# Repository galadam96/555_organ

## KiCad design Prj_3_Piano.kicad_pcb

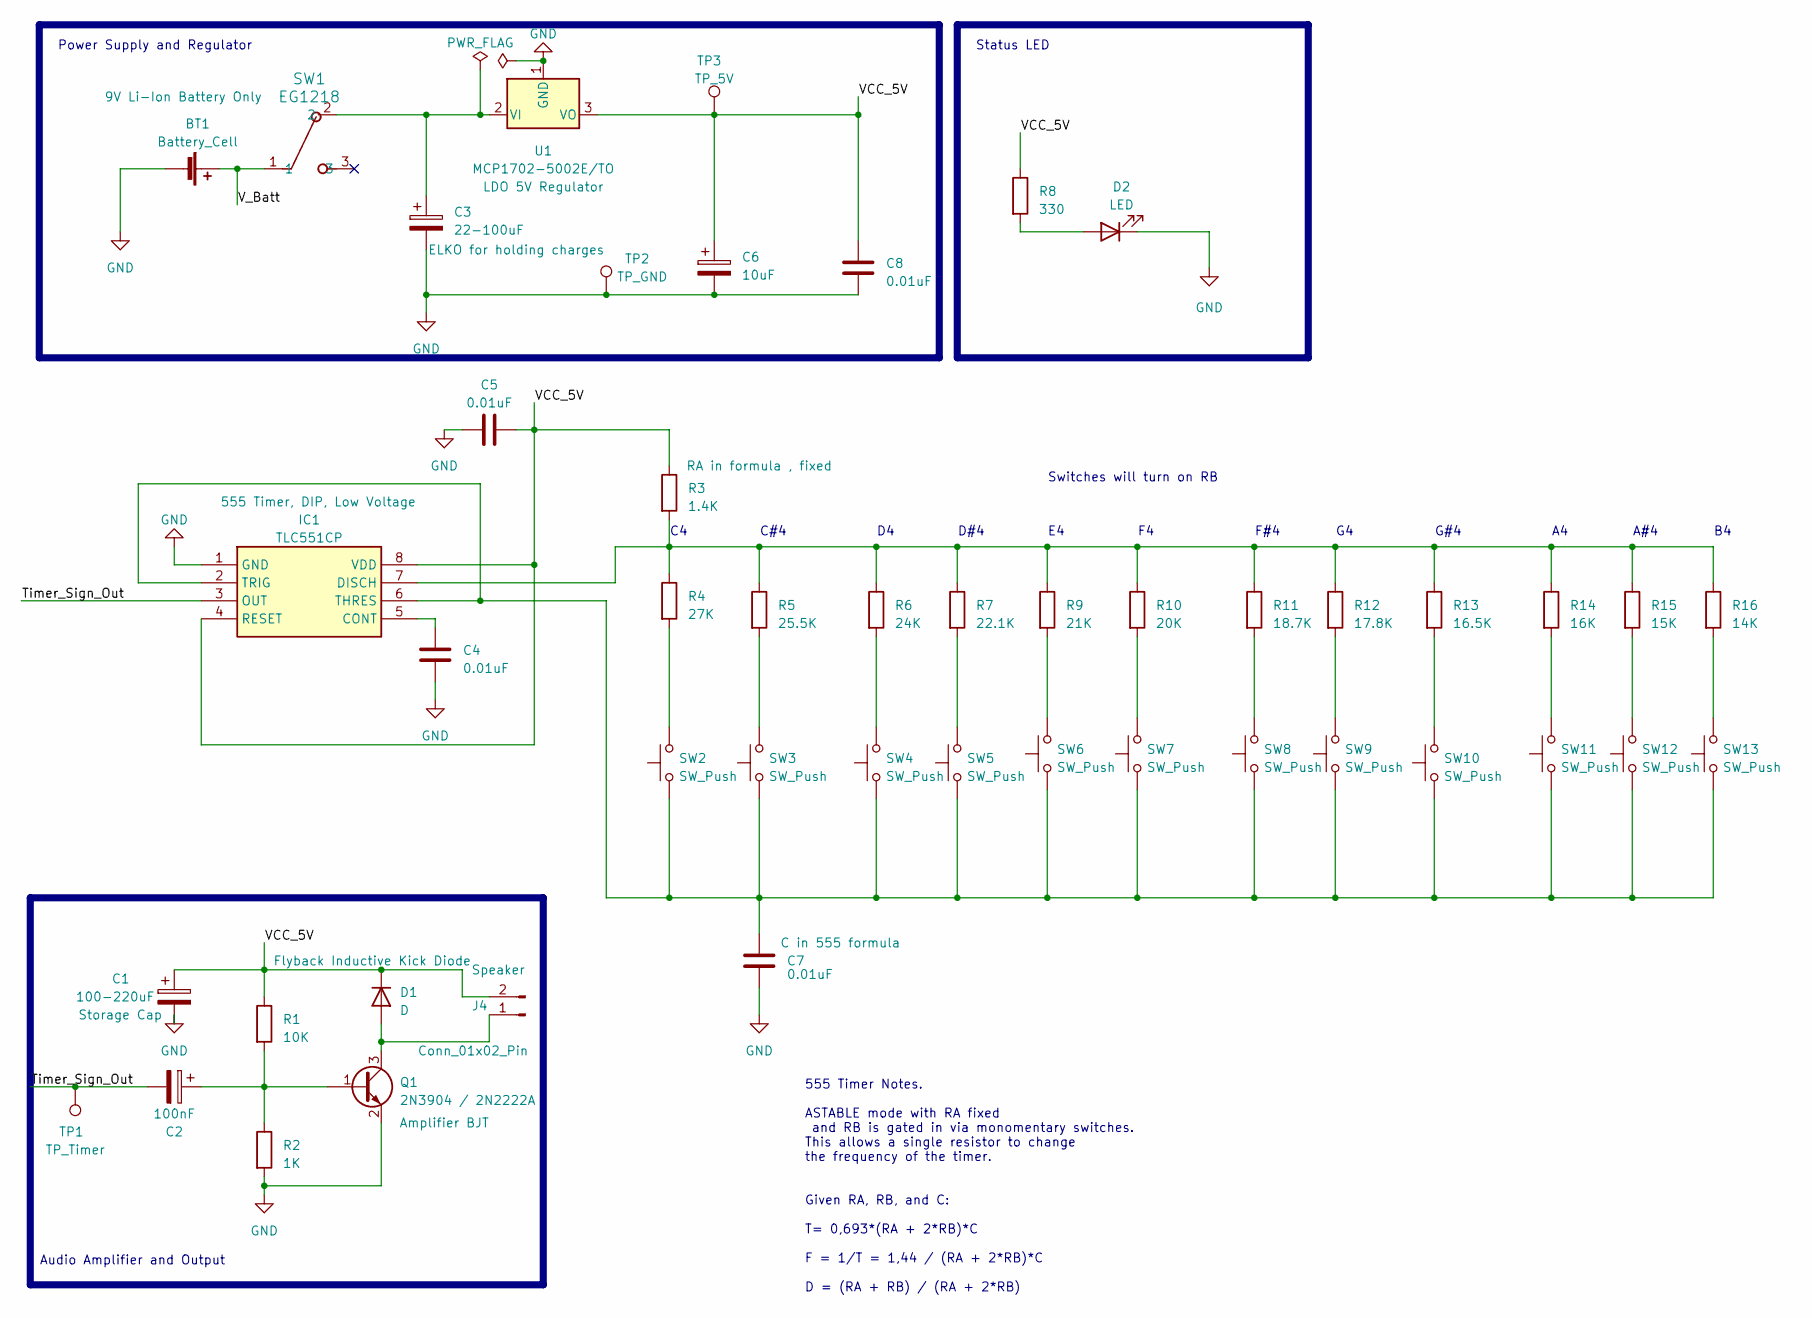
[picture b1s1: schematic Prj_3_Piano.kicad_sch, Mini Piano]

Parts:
BT1: Battery_Cell; KeyStone_1294_Battery_Holder
C1: 100-220uF; CP_Radial_D5.0mm_P2.00mm
C2: 100nF; CP_Radial_D5.0mm_P2.00mm
C3: 22-100uF; CP_Radial_D5.0mm_P2.00mm
C4, C5, C7, C8: 0.01uF; CP_Radial_D8.0mm_P5.00mm
C6: 10uF; CP_Radial_D5.0mm_P2.00mm
D1: D; D_DO-41_SOD81_P10.16mm_Horizontal
D2: LED; LED_D5.0mm
IC1: TLC551CP; Mouser Part Number 595-TLC551CP
J4: Conn_01x02_Pin; PinHeader_1x02_P2.54mm_Vertical
Q1: 2N3904 / 2N2222A; TO-92_Inline
R1: 10K; R_Axial_DIN0207_L6.3mm_D2.5mm_P10.16mm_Horizontal
R2: 1K; R_Axial_DIN0207_L6.3mm_D2.5mm_P10.16mm_Horizontal
R3: 1.4K; R_Axial_DIN0207_L6.3mm_D2.5mm_P10.16mm_Horizontal
R4: 27K; R_Axial_DIN0207_L6.3mm_D2.5mm_P10.16mm_Horizontal
R5: 25.5K; R_Axial_DIN0207_L6.3mm_D2.5mm_P10.16mm_Horizontal
R6: 24K; R_Axial_DIN0207_L6.3mm_D2.5mm_P10.16mm_Horizontal
R7: 22.1K; R_Axial_DIN0207_L6.3mm_D2.5mm_P10.16mm_Horizontal
R8: 330; R_Axial_DIN0207_L6.3mm_D2.5mm_P10.16mm_Horizontal
R9: 21K; R_Axial_DIN0207_L6.3mm_D2.5mm_P10.16mm_Horizontal
R10: 20K; R_Axial_DIN0207_L6.3mm_D2.5mm_P10.16mm_Horizontal
R11: 18.7K; R_Axial_DIN0207_L6.3mm_D2.5mm_P10.16mm_Horizontal
R12: 17.8K; R_Axial_DIN0207_L6.3mm_D2.5mm_P10.16mm_Horizontal
R13: 16.5K; R_Axial_DIN0207_L6.3mm_D2.5mm_P10.16mm_Horizontal
R14: 16K; R_Axial_DIN0207_L6.3mm_D2.5mm_P10.16mm_Horizontal
R15: 15K; R_Axial_DIN0207_L6.3mm_D2.5mm_P10.16mm_Horizontal
R16: 14K; R_Axial_DIN0207_L6.3mm_D2.5mm_P10.16mm_Horizontal
SW1: EG1218
SW2, SW3, SW4, SW5, SW6, SW7, SW8, SW9, SW10, SW11, SW12, SW13: SW_Push; SW_PUSH_6mm
TP1, TP2, TP3: TestPoint_Pad_2.0x2.0mm
U1: MCP1702-5002E/TO; TO-92_Inline

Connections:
/Timer_Sign_Out: C2.2, IC1.3 (OUT), TP1.1
/VCC_5V: C1.1, C5.2, C6.1, C8.1, D1.1 (K), IC1.4 (RESET), IC1.8 (VDD), R1.1, R3.1, R8.1, TP3.1, U1.3 (VO); also elsewhere on the board
/V_Batt: BT1.1 (+), SW1.1
GND: BT1.2 (-), C1.2, C3.2, C4.2, C5.1, C6.2, C7.2, C8.2, D2.1 (K), IC1.1 (GND), Q1.2 (E), R2.2, TP2.1, U1.1 (GND)
unnamed 4: D1.2 (A), Q1.3 (C); also elsewhere on the board
unnamed: D2.2 (A), R8.2
unnamed: C4.1, IC1.5 (CONT)
unnamed: IC1.7 (DISCH), R3.2, R4.1, R5.1, R6.1, R7.1, R9.1, R10.1, R11.1, R12.1, R13.1, R14.1, R15.1, R16.1
unnamed: C7.1, IC1.2 (TRIG), IC1.6 (THRES), SW2.1, SW3.1, SW4.1, SW5.1, SW6.1, SW7.1, SW8.1, SW9.1, SW10.1, SW11.1, SW12.1, SW13.1
unnamed: C2.1, Q1.1 (B), R1.2, R2.1
unnamed: R4.2, SW2.2
unnamed: R5.2, SW3.2
unnamed: R6.2, SW4.2
unnamed: R7.2, SW5.2
unnamed: R9.2, SW6.2
unnamed: R10.2, SW7.2
unnamed: R11.2, SW8.2
unnamed: R12.2, SW9.2
unnamed: R13.2, SW10.2
unnamed: R14.2, SW11.2
unnamed: R15.2, SW12.2
unnamed: R16.2, SW13.2
unnamed: C3.1, SW1.2, U1.2 (VI)

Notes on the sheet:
Audio Amplifier and Output
D#4
F#4
A#4
C#4
Switches will turn on RB
Power Supply and Regulator
G#4
555 Timer Notes. ASTABLE mode with RA fixed and RB is gated in via monomentary switches. This allows a single resistor to change the frequency of the timer. Given RA, RB, and C: T= 0,693*(RA + 2*RB)*C F = 1/T = 1,44 / (RA + 2*RB)*C D = (RA + RB) / (RA + 2*RB)
Status LED

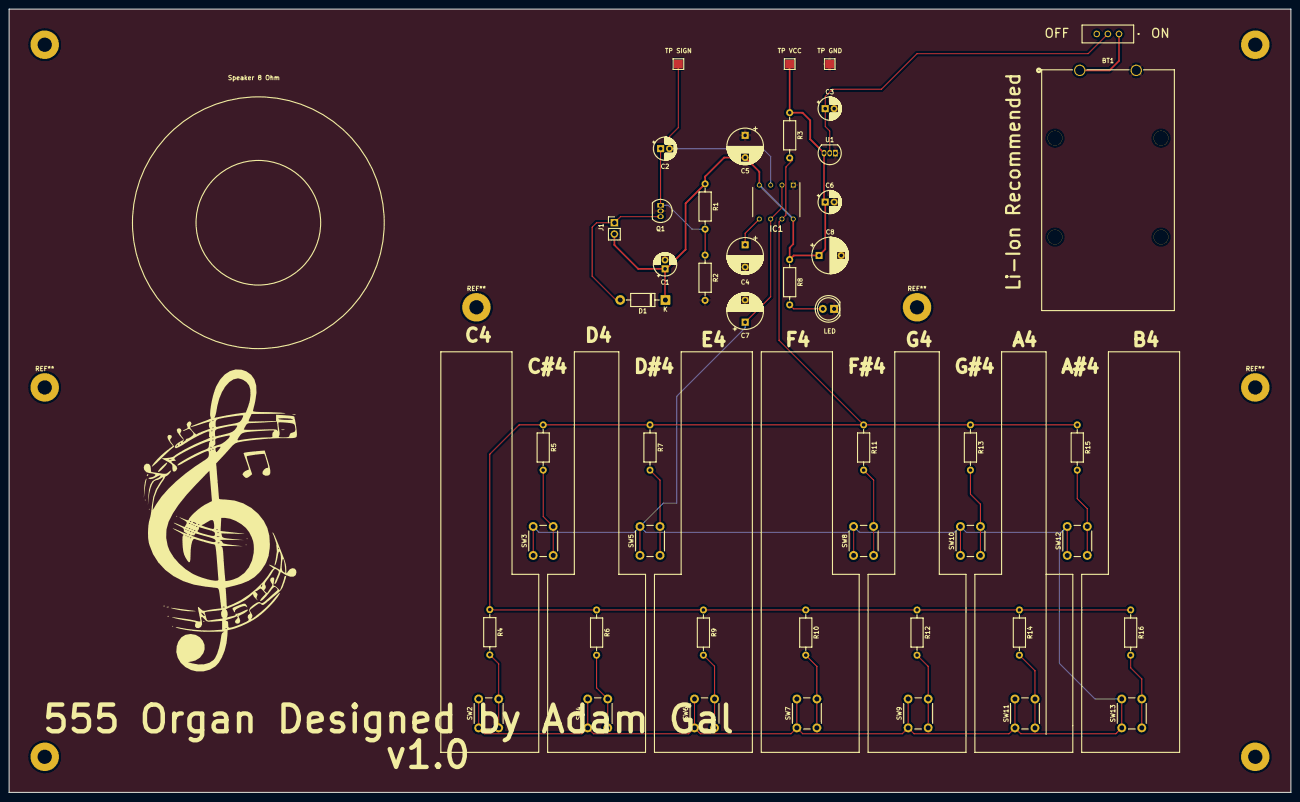
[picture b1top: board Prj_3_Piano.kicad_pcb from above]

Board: 2 copper layers, 288.0 x 176.0 mm, 47 parts (0 on the bottom side), 23 nets.

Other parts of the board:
J1: Conn_01x02_Pin; PinHeader_1x02_P2.54mm_Vertical

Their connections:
/VCC_5V: J1.2; also elsewhere on the board
unnamed 4: J1.1; also elsewhere on the board

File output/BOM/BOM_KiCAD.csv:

"Id";"Designator";"Footprint";"Quantity";"Designation";"Supplier and ref";
1;"R13";"R_Axial_DIN0207_L6.3mm_D2.5mm_P10.16mm_Horizontal";1;"16.5K";;;
2;"R1";"R_Axial_DIN0207_L6.3mm_D2.5mm_P10.16mm_Horizontal";1;"10K";;;
3;"R8";"R_Axial_DIN0207_L6.3mm_D2.5mm_P10.16mm_Horizontal";1;"330";;;
4;"SW5,SW2,SW6,SW8,SW3,SW4,SW10,SW11,SW7,SW13,SW12,SW9";"SW_PUSH_6mm";12;"SW_Push";;;
5;"R10";"R_Axial_DIN0207_L6.3mm_D2.5mm_P10.16mm_Horizontal";1;"20K";;;
6;"C7,C5,C8,C4";"CP_Radial_D8.0mm_P5.00mm";4;"0.01uF";;;
7;"Q1";"TO-92_Inline";1;"2N3904 / 2N2222A";;;
8;"R2";"R_Axial_DIN0207_L6.3mm_D2.5mm_P10.16mm_Horizontal";1;"1K";;;
9;"D1";"D_DO-41_SOD81_P10.16mm_Horizontal";1;"D";;;
10;"TP2,TP3,TP1";"TestPoint_Pad_2.0x2.0mm";3;"~";;;
11;"IC1";"TLC551CP";1;"TLC551CP";;;
12;"R9";"R_Axial_DIN0207_L6.3mm_D2.5mm_P10.16mm_Horizontal";1;"21K";;;
13;"C6";"CP_Radial_D5.0mm_P2.00mm";1;"10uF";;;
14;"U1";"TO-92_Inline";1;"MCP1702-5002E/TO";;;
15;"R5";"R_Axial_DIN0207_L6.3mm_D2.5mm_P10.16mm_Horizontal";1;"25.5K";;;
16;"R6";"R_Axial_DIN0207_L6.3mm_D2.5mm_P10.16mm_Horizontal";1;"24K";;;
17;"R12";"R_Axial_DIN0207_L6.3mm_D2.5mm_P10.16mm_Horizontal";1;"17.8K";;;
18;"D2";"LED_D5.0mm";1;"LED";;;
19;"R15";"R_Axial_DIN0207_L6.3mm_D2.5mm_P10.16mm_Horizontal";1;"15K";;;
20;"BT1";"KeyStone_1294_Battery_Holder";1;"Battery_Cell";;;
21;"C1";"CP_Radial_D5.0mm_P2.00mm";1;"100-220uF";;;
22;"R7";"R_Axial_DIN0207_L6.3mm_D2.5mm_P10.16mm_Horizontal";1;"22.1K";;;
23;"C3";"CP_Radial_D5.0mm_P2.00mm";1;"22-100uF";;;
24;"R16";"R_Axial_DIN0207_L6.3mm_D2.5mm_P10.16mm_Horizontal";1;"14K";;;
25;"C2";"CP_Radial_D5.0mm_P2.00mm";1;"100nF";;;
26;"R14";"R_Axial_DIN0207_L6.3mm_D2.5mm_P10.16mm_Horizontal";1;"16K";;;
27;"R11";"R_Axial_DIN0207_L6.3mm_D2.5mm_P10.16mm_Horizontal";1;"18.7K";;;
28;"SW1";"EG1218";1;"EG1218";;;
29;"R3";"R_Axial_DIN0207_L6.3mm_D2.5mm_P10.16mm_Horizontal";1;"1.4K";;;
30;"R4";"R_Axial_DIN0207_L6.3mm_D2.5mm_P10.16mm_Horizontal";1;"27K";;;
31;"J1";"PinHeader_1x02_P2.54mm_Vertical";1;"Conn_01x02_Pin";;;

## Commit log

2023-06-29 Added first version
